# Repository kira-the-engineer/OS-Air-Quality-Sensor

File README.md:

# OS-Air-Quality-Sensor

## Project Description
 The goal of this project is to create a low cost, relatively accurate air quality sensor in a small form factor. It is inspired by seeing popular air quality sensors like the Aranet and wanting to make something more open source and accessible to people. The sensor chosen is a Sensirion SCD-40, which is a infrared CO2 sensor with an accuracy of +/- 5% for concentrations of CO2 between 400-2000 PPM. It's lower cost than a more accuarate sensor, but good enough to accurately measure air quality in most settings. The carrier board and display for the sensor will be kept small and simple, about the size of a cassette tape. Design constraints for this project were chosen to maintain accuracy while keeping the cost of manufacturing the board under $100. 

### Design Constraints

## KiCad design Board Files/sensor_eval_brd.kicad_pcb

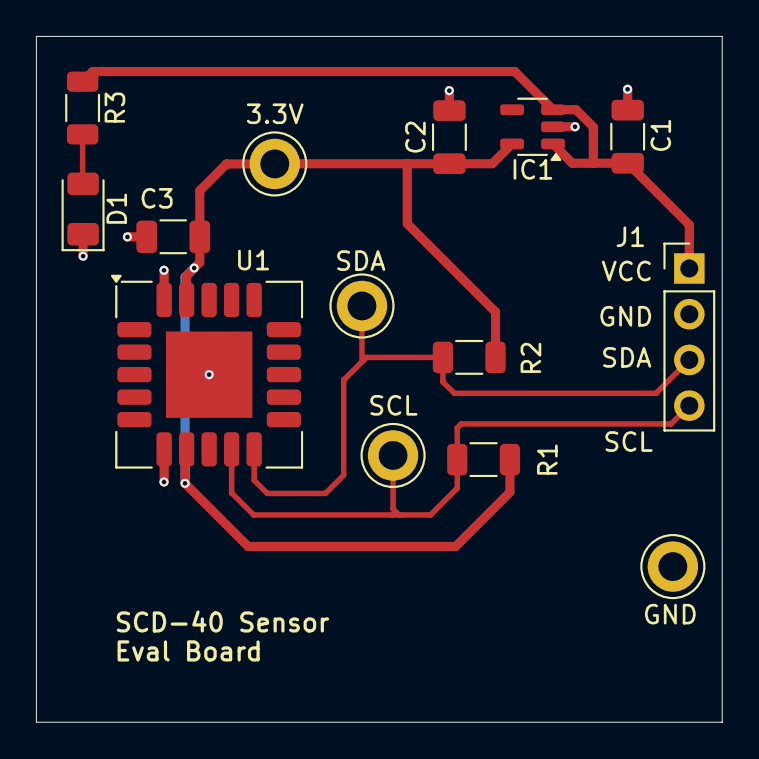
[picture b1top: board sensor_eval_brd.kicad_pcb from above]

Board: 2 copper layers, 38.1 x 38.1 mm, 14 parts (0 on the bottom side), 6 nets.

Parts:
3.3V: TestPoint; TestPoint_Keystone_5005-5009_Compact
C1, C2: 1uF; C_1206_3216Metric
C3: 100nF; C_1206_3216Metric
D1: LED; LED_1206_3216Metric
GND: TestPoint; TestPoint_Keystone_5005-5009_Compact
IC1: TPS7A0333PDBVR; SOT-23-5
J1: Conn_01x04; PinHeader_1x04_P2.54mm_Vertical
R1, R2: 10k; R_1206_3216Metric
R3: 150; R_1206_3216Metric
SCL: TestPoint; TestPoint_Keystone_5005-5009_Compact
SDA: TestPoint; TestPoint_Keystone_5005-5009_Compact
U1: SCD40-D-R2; Sensirion_SCD4x-1EP_10.1x10.1mm_P1.25mm_EP4.8x4.8mm

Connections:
/3.3V: 3.3V.1, C2.1, C3.1, IC1.5 (OUT), R1.1, R2.1, U1.7 (VDD), U1.19 (VDDH)
/SCL: J1.4, R1.2, SCL.1, U1.9 (SCL)
/SDA: J1.3, R2.2, SDA.1, U1.10 (SDA)
GND: C1.2, C2.2, C3.2, D1.1 (K), GND.1, IC1.2 (GND), J1.2, U1.6 (GND), U1.20 (GND), U1.21 (GND)
unnamed: D1.2 (A), R3.2
VCC: C1.1, IC1.1 (IN), IC1.3 (EN), J1.1, R3.1

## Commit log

2025-05-31 Uploads for Sensor Eval Board
    Uploaded gerbers, schematics, and pcb files for the little evaluation board I created to test out the SCD-40 before creating the final PCB
2025-05-31 Update README.md
    Add extended project description
